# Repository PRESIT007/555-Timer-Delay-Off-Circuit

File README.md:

# 555 Timer Delay-Off Timer

A practical electronics learning project exploring **delay-off timer operation, relay control, and PCB design** using a 555 timer IC and KiCad.

This project is part of my learning journey as an Electrical Engineering student. The goal is to understand how a timer circuit works, how its components determine the delay, and how a circuit moves from a schematic to a PCB layout.

> **Important:** Confirm the exact timing behavior and formula against the final schematic and practical test. The operation depends on how the 555 timer, trigger, RC network, and relay interface are connected.

## 1. Project Objectives

- Understand the 555 timer IC and its timing function.
- Learn how resistor-capacitor (RC) networks create a time delay.
- Study push-button triggering and relay switching.
- Design and document a circuit in KiCad.
- Explore schematic capture, PCB layout, and 3D board visualization.
- Prepare a Bill of Materials (BOM) and PCB manufacturing outputs.
- Practice testing, troubleshooting, and documenting an electronics project.

## 2. What Is a Delay-Off Timer?

A delay-off timer keeps a load operating for a defined period and then switches it OFF. Depending on the design, the delay may begin when a trigger is applied or when a control signal is removed.

In a relay-based circuit, relay contacts can switch a separate load. The relay's input polarity and the timer's output interface determine how the load behaves during the timing interval.

Confirm the exact sequence for this circuit against the schematic and practical test: what happens at power-up, when the button is pressed, and when the delay expires.

## 3. Working Principle of the 555 Timer

The 555 timer contains internal comparators, a latch, and a discharge transistor. These monitor the timing capacitor voltage and control the output state.

In a common monostable configuration:
1. A trigger pulse changes the output state.
2. The timing capacitor charges through a resistor.
3. The 555 monitors the capacitor voltage against an internal threshold.
4. When the threshold is reached, the output returns to its original state and the capacitor is discharged.

The external circuit configuration determines whether this sequence matches the intended delay-off behavior.

## 4. RC Timing Concept

A resistor-capacitor (RC) network sets the time required for the capacitor voltage to change.

For a conventional 555 monostable circuit, the approximate pulse duration is:

**T ≈ 1.1 × R × C**

Where:
- **T** is the timing interval in seconds.
- **R** is the effective timing resistance in ohms.
- **C** is the timing capacitance in farads.

This formula applies only to the corresponding monostable topology. Other 555 configurations can use different timing relationships. Actual timing varies with component tolerances, capacitor leakage, supply voltage, temperature, and circuit implementation.

## 5. Circuit Features

- 555 timer-based timing control
- Push-button trigger, as shown in the schematic
- Relay-based switching interface
- Adjustable timing only if an adjustment component is present in the final design
- KiCad schematic and PCB layout
- 3D PCB visualization
- BOM and Gerber manufacturing files

## 6. Main Components

Refer to the actual schematic and `BOM.csv` for confirmed values, quantities, footprints, and part numbers.

| Component | Purpose |
|---|---|
| 555 timer IC | Generates the timing response |
| Timing resistor(s) | Control capacitor charging or discharging rate |
| Timing capacitor | Stores charge and establishes the interval |
| Push button / trigger input | Initiates the timing sequence, according to the circuit |
| Relay or relay module | Switches the external load |
| Power supply and connectors | Provide power and circuit connections |
| PCB and footprints | Provide the physical circuit layout |

Verify all component values against the final schematic before assembly.

## 7. Design Files and Previews

### Circuit schematic

[Open the schematic PDF](schematic.pdf)

### PCB layout

### 3D PCB views

Update image paths if your repository uses different folders or filenames.

## 8. Repository Structure

This is a suggested structure. Keep the paths consistent with the files uploaded to GitHub.

```text
555-Timer-Delay-Off-Circuit/
├── README.md
├── schematic.pdf
├── BOM.csv
├── Gerber.zip
├── KiCad/
│   ├── delay off timer ckt.kicad_pro
│   ├── delay off timer ckt.kicad_sch
│   └── delay off timer ckt.kicad_pcb
└── Images/
    ├── schematic.png
    ├── pcb-layout.png
    ├── 1_pcb-3d.png
    └── 2_pcb-3d.png
```

- `.kicad_pro` — KiCad project settings
- `.kicad_sch` — editable schematic
- `.kicad_pcb` — editable PCB layout
- `schematic.pdf` — printable schematic
- `BOM.csv` — component list
- `Gerber.zip` — manufacturing outputs, if it contains exported Gerber and drill files

## 9. Software and Tools

- **KiCad EDA** — schematic capture, PCB layout, and 3D board inspection
- **555 timer IC** — timing and control
- **RC timing network** — sets the capacitor voltage transition
- **Relay interface** — switches a load within its ratings

## 10. How to Open the Design

1. Download or clone the repository.
2. Open the `.kicad_pro` file in KiCad.
3. Open the schematic to study connections and component values.
4. Open the PCB layout to inspect footprints, routing, board outline, and silkscreen.
5. Open the 3D Viewer to inspect the board representation.
6. Include any custom symbols, footprints, or 3D models needed by the design.

## 11. Testing and Validation

- [ ] Schematic reviewed
- [ ] KiCad Electrical Rules Checker (ERC) results reviewed
- [ ] KiCad PCB Design Rules Checker (DRC) results reviewed
- [ ] Footprints and connector pinouts verified
- [ ] Supply voltage and component ratings verified
- [ ] Relay input polarity and startup state tested
- [ ] Button-trigger sequence tested
- [ ] Actual delay measured and recorded
- [ ] Relay switches at the intended point in the sequence
- [ ] 3D view checked against component placement

A useful experiment is to measure the delay several times, calculate the average, and compare it with the theoretical value from the correct circuit equation. Record differences and consider component tolerances and circuit topology.

## 12. Applications

- Timed relay control
- Automatic switching
- Small automation experiments
- Educational electronics laboratories
- Control of suitable low-voltage loads

Application suitability depends on the circuit ratings and tested behavior.

## 13. Safety Notes

- Start with a suitable low-voltage, current-limited supply.
- Use a safe low-voltage load during initial tests.
- Check relay module supply requirements and contact ratings.
- Never exceed component voltage or current ratings.
- For mains switching, use suitable isolation, enclosure, fusing, clearances, and qualified supervision. Never touch exposed mains wiring while powered.

## 14. Learning Outcomes

Through this project, I am learning to:
- Connect circuit theory with practical electronics.
- Understand 555 timer operation and RC timing.
- Read and create electronic schematics.
- Design a PCB and inspect it in 3D.
- Prepare technical documentation and manufacturing files.
- Test circuit behavior and troubleshoot differences between theory and practice.

## License

This project's hardware design files, including the KiCad schematic and PCB layout, are licensed under the **CERN Open Hardware Licence Version 2 – Strongly Reciprocal (CERN-OHL-S-2.0)**.

You may use, study, modify, and redistribute the covered design files under the terms of this license. Modified versions of the covered hardware design must comply with its applicable reciprocal-sharing requirements.

See the [full CERN-OHL-S-2.0 license](https://ohwr.org/cern_ohl_s_v2.txt) for details.
 
---

**Project type:** Electrical Engineering · PCB Design · Analog Electronics · Timer Circuits · PCB Design  
**Design tool:** KiCad  
**Purpose:** Learning, experimentation, and documentation

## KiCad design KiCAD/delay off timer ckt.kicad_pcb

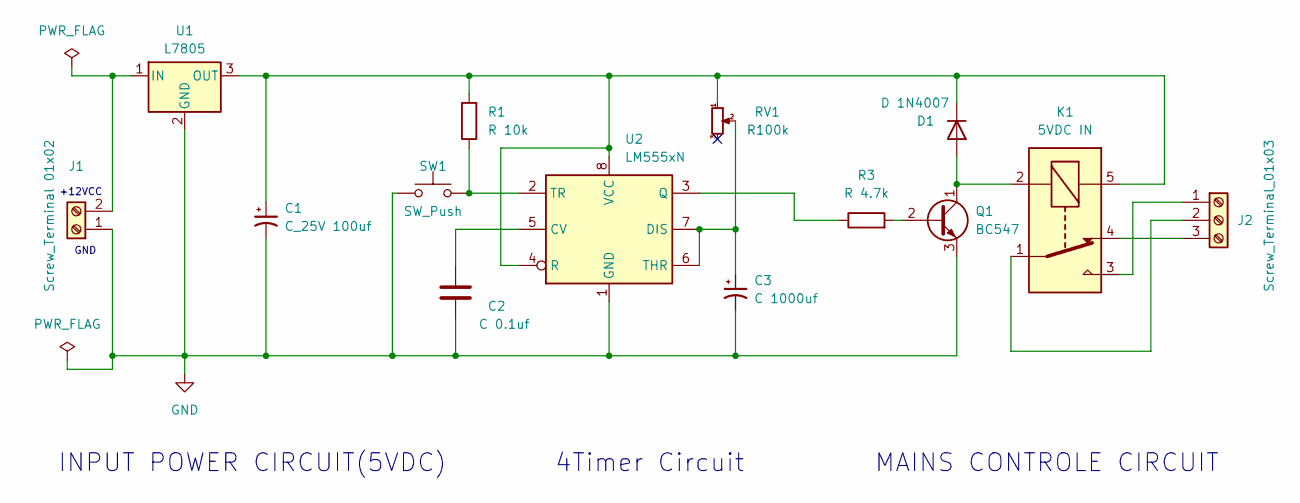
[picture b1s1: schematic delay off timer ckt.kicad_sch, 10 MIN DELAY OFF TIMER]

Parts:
C1: C_25V 100uf; CP_Radial_D10.0mm_P3.80mm
C2: C 0.1uf; Resonator-2Pin_W6.0mm_H3.0mm
C3: C 1000uf; CP_Radial_D14.0mm_P7.50mm
D1: D 1N4007; D_DO-15_P10.16mm_Horizontal
J1: Screw_Terminal 01x02; TerminalBlock_Phoenix_PT-1,5-2-5.0-H_1x02_P5.00mm_Horizontal
J2: Screw_Terminal_01x03; TerminalBlock_Phoenix_PT-1,5-3-5.0-H_1x03_P5.00mm_Horizontal
K1: 5VDC IN; Relay_SPDT_SANYOU_SRD_Series_Form_C
Q1: BC547; TO-92_Inline
R1: R 10k; R_Axial_DIN0207_L6.3mm_D2.5mm_P10.16mm_Horizontal
R3: R 4.7k; R_Axial_DIN0207_L6.3mm_D2.5mm_P10.16mm_Horizontal
RV1: R100k; Potentiometer_Bourns_3266Y_Vertical
SW1: SW_Push; SW_TH_Tactile_Omron_B3F-102x
U1: L7805; TO-220-3_Vertical
U2: LM555xN; DIP-8_W7.62mm

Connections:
GND: C1.2, C2.2, C3.2, J1.1, Q1.3 (E), SW1.1, U1.2 (GND), U2.1 (GND)
unnamed: D1.2 (A), K1.2, Q1.1 (C)
unnamed: C1.1, D1.1 (K), K1.5, R1.2, RV1.1, U1.3 (OUT), U2.4 (R), U2.8 (VCC)
unnamed: J1.2, U1.1 (IN)
unnamed: J2.1, K1.3
unnamed: J2.2, K1.1
unnamed: J2.3, K1.4
unnamed: Q1.2 (B), R3.2
unnamed: C2.1, U2.5 (CV)
unnamed: C3.1, RV1.2, U2.6 (THR), U2.7 (DIS)
unnamed: R3.1, U2.3 (Q)
unnamed: R1.1, SW1.2, U2.2 (TR)

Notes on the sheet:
4Timer Circuit
GND
+12VCC
INPUT POWER CIRCUIT(5VDC)
MAINS CONTROLE CIRCUIT

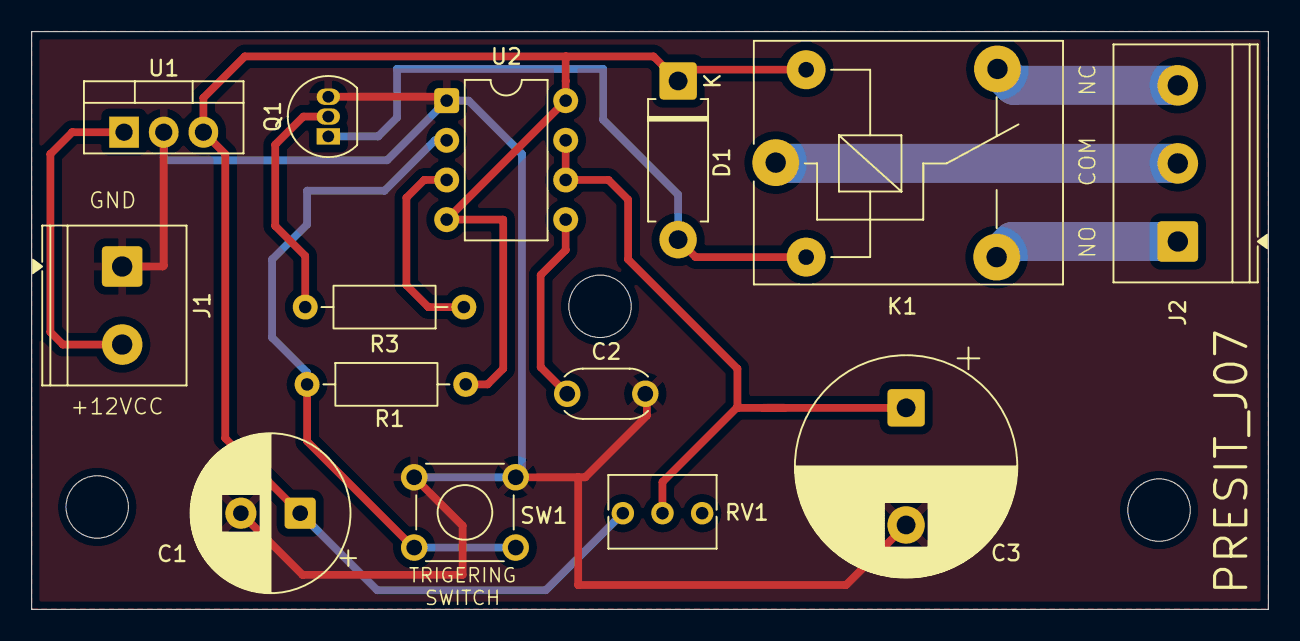
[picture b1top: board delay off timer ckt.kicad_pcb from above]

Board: 2 copper layers, 79.2 x 37.0 mm, 14 parts (0 on the bottom side), 12 nets.
